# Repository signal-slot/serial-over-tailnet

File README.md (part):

# serial-over-tailnet

[日本語](README-ja.md)

An ESP32-S3 board with PSRAM that joins a Tailscale network (a tailnet) on its own and bridges the serial console of a target SBC to a TCP port on the tailnet.
The console is a 3.3 V UART of the target (with a Seeed Studio XIAO ESP32S3 or ESP32C3) or one of its USB serial interfaces (with a YD-ESP32-S3).
The project was called usb-serial-over-tailscale until November 2026.

```text
Remote PC ──Tailscale / TCP:35930────▶ XIAO ESP32S3/C3 ──UART───▶ UART console of the target SBC
Remote PC ──Tailscale / TCP:35930+n──▶ YD-ESP32-S3 ───USB host──▶ serial interface n of the target SBC
Remote PC ──Tailscale / USB/IP 3240──▶ YD-ESP32-S3 ───USB host──▶ the whole USB device (a debug probe, for example)
```

Everything a Tailscale node needs (control protocol, WireGuard, DERP, NAT traversal) is implemented in Rust in this repository.
Initial setup is an interactive shell over USB serial; flashing and setup are done from a browser, with nothing to install.

## Status

Working end to end:

- Wi-Fi setup through the wizard and joining a tailnet with the approval URL.
- `tailscale ping` from another node, both via DERP and over a direct path.
- With a XIAO ESP32S3: the console of a Raspberry Pi 5 over its 3.3 V UART (the 3-pin debug connector).
- With a XIAO ESP32C3 (no PSRAM): joining a tailnet of 50 peers, its DERP connection, 300 bridge connections in a row with memory steady, its UART in a loopback (D10 wired to D8) over the tailnet, and the console of a NanoPC-T6 on its 3.3 V debug UART at 1500000 baud, the line set by pyserial's `rfc2217://`.
- With a YD-ESP32-S3: console access to a Raspberry Pi Debug Probe (CDC-ACM) and a Toradex Dahlia (FT4232H) over USB.
- RFC 2217 sessions against both USB targets: baud rate and framing changes, DTR and RTS, break and purge from pyserial.
- On the FT4232H, three ports claimed at once and a client on the fourth port refused.
- Recovery after adapter reboot, Wi-Fi reconnection and USB replug.
- With a YD-ESP32-S3 in USB/IP mode: the MCU-Link of an FRDM-MCXN947 attached on a Linux PC with `usbip attach`, probe-rs erasing the MCXN947, writing 712 KB to its flash and verifying it, and the board's console on the MCU-Link's serial port.

Not yet:

- Headless registration with an auth key.
- CP210x, CH340/CH341, and non-H-series FTDI chips such as the FT232R.
- Recovery after a reboot of the target SBC, an internet outage, or an unreachable control server.
- Long-running operation, behaviour after node key expiry (180 days by default), and reboots triggered by the task watchdog.
- esptool through RFC 2217 (its DTR and RTS sequence is tested on the host with `cargo run -p adapter-core --example rfc2217_sim`).

### Boards and images

Flash size and PSRAM mode are build-time settings, so CI builds one image per board and module (`firmware/variants/`).
PSRAM is required on the ESP32-S3 boards: network thread stacks, TLS buffers and most of the heap live there.
The ESP32-C3 has none; its image is built with smaller stacks and buffers (feature `small-ram` of tsnode), and about 40 KB of its RAM stays free on a tailnet of 50 peers.

| Image | Board | Flash | PSRAM | Status |
| --- | --- | --- | --- | --- |
| `xiao-s3` | Seeed Studio XIAO ESP32S3 | 8 MB | 8 MB octal | supported |
| `xiao-c3` | Seeed Studio XIAO ESP32C3 | 4 MB | none | supported (UART tried in a loopback) |
| `n16r8` | YD-ESP32-S3 with an N16R8 module | 16 MB | 8 MB octal | supported |
| `n8r2` | YD-ESP32-S3 with an N8R2 module | 8 MB | 2 MB quad | supported |
| `n8r8` | YD-ESP32-S3 with an N8R8 module | 8 MB | 8 MB octal | built |
| | modules without PSRAM (N4, N8, N16) | | none | not supported |

To build an image locally, point esp-idf-sys at its defaults file and pass its name to the image script.
The XIAO's image also needs its feature; the ESP32-C3 is another target and is built without the USB host component:

```bash
cd firmware
ESP_IDF_SDKCONFIG_DEFAULTS="sdkconfig.defaults;variants/xiao-s3.defaults" cargo build --release --features board-xiao-s3
tools/mkimage.sh xiao-s3 release

MCU=esp32c3 ESP_IDF_SYS_EXTRA_COMPONENTS_FILE="$PWD/variants/no-extra-components.toml" \
ESP_IDF_SDKCONFIG_DEFAULTS="sdkconfig.defaults;variants/xiao-c3.defaults" \
  cargo build --release --features board-xiao-c3 --target riscv32imc-esp-espidf
tools/mkimage.sh xiao-c3 release

ESP_IDF_SDKCONFIG_DEFAULTS="sdkconfig.defaults;variants/n8r2.defaults" cargo build --release
tools/mkimage.sh n8r2 release
```

## Layout

| Path | Role |
| --- | --- |
| `crates/tsnode` | Tailscale node: control plane (ts2021 Noise and a minimal HTTP/2), WireGuard, DERP, disco, STUN, TCP termination with smoltcp. Runs on a host and on ESP-IDF. |
| `crates/adapter-core` | Interactive setup shell. I/O and device operations are traits, so the wizard is unit-tested on the host. |
| `tools/hostnode` | Runs tsnode on Linux for verification: joins a real tailnet and serves an echo server. |
| `firmware` | ESP32-S3 and ESP32-C3 firmware (esp-idf-svc): setup console, UART bridge (XIAO ESP32S3 and ESP32C3), USB host (YD-ESP32-S3: CDC-ACM, FTDI, CP210x, CH34x), Wi-Fi, Tailscale node, TCP bridge. |
| `hardware/case` | 3D-printed case for the YD-ESP32-S3: OpenSCAD source and ready-to-print STLs, with and without pin headers ([README](hardware/case/README.md)). |
| `hardware/xiao-carrier` | Carrier board for the XIAO ESP32S3 with level translation and a 4-pin header; designed, not made ([README](hardware/xiao-carrier/README.md)). |
| `hardware/board` | Our own adapter board around the ESP32-S3-MINI-1; ordered, not yet verified ([README](hardware/board/README.md)). |

tsnode is split into these modules.

| Module | Contents |
| --- | --- |
| `controlbase`, `h2`, `control` | `/key` fetch, Noise IK handshake over `POST /ts2021`, `/machine/register` and `/machine/map` over HTTP/2. `/key` is always TLS; the Noise transport tries plain :80 first and falls back to TLS. |
| `wireguard` | Noise IKpsk2 handshake (initiator and responder), transport, replay window, rekey and keepalive timers. |
| `derp` | DERP relay client (TLS, fast-start, ping/pong, NotePreferred). |
| `disco`, `stun` | ping, pong and call-me-maybe for direct paths; public endpoint discovery with STUN. |
| `magicsock` | Path selection between UDP and DERP, handshake handling, peer table. |
| `netstack` | TCP termination on the tailnet addresses with smoltcp. |
| `node` | Ties the above together in threads. Keys persist in NVS or a file. |

## Usage

### Prepare the board

Two boards can be used; which one depends on where the target's console is.

| Board | Bridges | Soldering |
| --- | --- | --- |
| Seeed Studio XIAO ESP32S3 | a 3.3 V UART of the target (pins or a debug connector) | none on a board that comes with pin headers |
| Seeed Studio XIAO ESP32C3 | the same, on other pins | the same |
| YD-ESP32-S3 | a USB serial interface of the target (its debug USB port) | required (the `USB-OTG` pad on the back) |

#### Seeed Studio XIAO ESP32S3

Buy a [Seeed Studio XIAO ESP32S3](https://www.seeedstudio.com/XIAO-ESP32S3-p-5627.html).
It has one USB-C port and no USB host role here: it bridges a **3.3 V UART** instead of a USB serial adapter, on port 35930.
Use it when the target has a UART on pins or a debug connector, such as the 3-pin debug connector of a Raspberry Pi 5.

| XIAO pin | Role | Connect to |
| --- | --- | --- |
| `GND` | ground | the target's GND |
| `3V3` | not used | leave unconnected |
| `D10` | TX (out of the XIAO) | the target's RX |
| `D9` | RX (into the XIAO) | the target's TX |

The four pins are next to each other on one side of the board (from the USB-C end: 5V, GND, 3V3, D10, D9, D8, D7).
On a board that comes with pin headers, jumper wires plug straight onto them; on a bare board, solder a 4-pin socket or pin header there.
The UART is 3.3 V only: do not connect 5 V or RS-232 signals, and put a level translator in between for a 1.8 V target.
Attach the antenna that comes with the board.

On the installer page it is the first entry under "Choose your board".
If no serial port appears, hold the `B` (BOOT) button while plugging the board in.
The USB port stays the setup console after setup as well (there is no second port), and it powers the board: a charger or a USB port of the target will do.
The baud rate is set with `baud` (115200 by default) or by an RFC 2217 client; there are no DTR and RTS lines.

Verified with the plain XIAO ESP32S3 on a Raspberry Pi 5; the Sense and Plus versions have not been tried.
The firmware limits the Wi-Fi transmit power to 15 dBm on this board: at 19.5 dBm and above it did not get past association with two access points, and at 18 dBm and below it did.
In Japan the board is sold with 技適: construction design certification number 217-230892, as [Akizuki Denshi lists it](https://akizukidenshi.com/catalog/g/g118078/). Elsewhere, check the marking on the board and the rules that apply to you.
[`hardware/xiao-carrier/`](hardware/xiao-carrier/) is a small carrier board for it (not made yet).

#### Seeed Studio XIAO ESP32C3

The [XIAO ESP32C3](https://wiki.seeedstudio.com/XIAO_ESP32C3_Getting_Started/) has the same outline and is used the same way, with these differences:

| XIAO pin | Role | Connect to |
| --- | --- | --- |
| `GND` | ground | the target's GND |
| `D10` | TX (out of the XIAO) | the target's RX |
| `D9` | not used | leave unconnected |
| `D8` | RX (into the XIAO) | the target's TX |

The pins are on the same side as on the S3 (from the USB-C end: 5V, GND, 3V3, D10, D9, D8, D7); a 5-pin socket from GND to D8 covers them.
RX is on D8 instead of D9 because the C3's D9 is GPIO9: the BOOT button pulls it to ground, and the chip starts in download mode if it is low at reset.
The carrier board connects D9, so it does not fit the C3.

Its ESP32-C3 has no PSRAM, so the firmware keeps less: only a few endpoints per peer, a peer's WireGuard state only once the peer talks to it, and a TCP window of 2 KB on the tailnet.
It has joined a tailnet of 50 peers with about 40 KB of RAM to spare; a much larger tailnet may not fit.
Its UART has been tried in a loopback, not yet against a target.
In Japan the board is sold with 技適: construction design certification number 204-B00704, as [Akizuki Denshi lists it](https://akizukidenshi.com/catalog/g/g117454/).

#### YD-ESP32-S3

Buy the [**YD-ESP32-S3** from VCC-GND Studio (its page on AliExpress)](https://www.aliexpress.com/item/1005004025123046.html).
On that page choose **N16R8** or **N8R2**: those two are supported.
The board has two USB-C ports, labelled `COM` and `USB` ([photos and documents from its maker](https://github.com/vcc-gnd/YD-ESP32-S3)).

**A note on radio certification.** The YD-ESP32-S3 is a good, inexpensive board. One thing to know before buying: its Wi-Fi module (marked `ESP32-S3-N16R8` or `ESP32-S3-N8R2`) is not one of Espressif's certified modules. It has no Japanese 技適 (we looked it up in the MIC database), and we have not found a radio certification for it in any other country either. Whether that matters depends on where you are: many countries put the obligation on sellers rather than on hobbyists, so please check the rules that apply to you. In Japan, the Radio Act asks the user's own equipment to carry the 技適 mark, so this board cannot be used there; for Japan we are making a board around the certified ESP32-S3-MINI-1 module, see [`hardware/board/`](hardware/board/) (designed and ordered in November 2026, not yet verified).

Short the `USB-OTG` solder pad on the back of the board (shown below before bridging).

This is required: it feeds 5 V from the board to the target's USB port, and without it the target chip never powers up and is never detected.
The two ports have fixed roles: **`COM` = 5 V power in** (a charger or a PC), **`USB` = the SBC** (the target's debug USB port). For flashing and setup, `COM` goes to the PC (it powers the board as well); `USB` can stay on the SBC.
See "Power and wiring" below for the safety rule that follows from it.

### Flash from a browser

Open [signal-slot.github.io/serial-over-tailnet](https://signal-slot.github.io/serial-over-tailnet/) in Chrome or Edge to flash and configure the board without installing anything.
The page opens the board's serial port with WebSerial and writes the CI-built binaries with ESP Web Tools (esptool-js).
A terminal on the same page runs the setup wizard.
It works on Windows 10 and later, macOS, Linux and ChromeOS; it does not work in Firefox, Safari or on phones.

Choose the board at the top of the page.

- **XIAO ESP32S3**: connect its USB-C port to the PC. It shows up as `USB JTAG/serial debug unit` (303a:1001). If no port appears, unplug it, hold the `B` (BOOT) button and plug it in again.
- **YD-ESP32-S3**: choose the module from the marking on its metal can (for example `ESP32-S3-N16R8`) and connect the `COM` port (CH343, 1a86:55d3). It flashes through the board's auto-download circuit, carries the boot log, and the target can stay plugged into the native port. The native port (303a:1001) works too and starts the wizard as soon as a terminal opens, but it disappears when setup completes and the port becomes the USB host; use it if the operating system does not list the COM port.

CI (GitHub Actions) builds every image on each push. Tags matching `v*` also attach `serial-over-tailnet-<image>.bin` (bootloader, partition table and app merged into one file) to a release.
The merged file can be written with `esptool write_flash 0x0`, but it also overwrites the NVS area with 0xFF, which erases the configuration and registration.
Updates from the page write only the three regions and keep the configuration.

### Initial setup

An unconfigured board plugged into a PC shows up as a USB serial port (Espressif USB JTAG/serial, 303a:1001): the XIAO's only port, the YD-ESP32-S3's native port.
Open it in a terminal and press Enter to start the wizard.
On the XIAO this port stays the shell after setup too, quiet until a command is typed.
On the YD-ESP32-S3 the COM port carries the same shell at 115200 together with the log output; it stays quiet until Enter, and `setup` starts the wizard there.

```bash
screen /dev/ttyACM0 115200
```

Leave DTR and RTS as a terminal leaves them, both asserted.
On these ports they reset the chip and select its boot mode, so a tool that
drives them apart resets the board, possibly into the ROM download mode, where
it goes quiet and answers nothing.

```text
serial-over-tailnet 0.1.0 - setup mode
Press Enter to start setup, or type a command:
=== Setup ===
Scanning Wi-Fi...
   1) home-wifi        (-48 dBm)
Select network number, or type an SSID (Enter to rescan, q to quit): 1
Password for home-wifi: ********
Connected (192.168.1.42)
Hostname on the tailnet [target-console]:
Registering with Tailscale... (press q to stop waiting)
Open this URL in a browser to approve the device:
  https://login.tailscale.com/a/xxxxxxxx
Waiting for approval...
Tailscale is up: target-console.example.ts.net 100.x.y.z
Setup complete. Reboot into normal mode now? [Y/n]
```

`setup` only adds a Wi-Fi network when the hostname and the Tailscale registration are already done.
`setup all` starts over.
To use an auth key, run `authkey tskey-auth-...` and then `login`.

The main commands are listed below; `help` prints the full list.

| Command | Description |
| --- | --- |
| `wifi <ssid> <pw>` | Add a Wi-Fi network and connect. Several can be stored; the strongest known AP is chosen at boot and on reconnect. |
| `wifi list`, `wifi forget <ssid>` | List and remove stored networks. |
| `port <n>`, `baud <rate>` | TCP port (default 35930; on the YD-ESP32-S3, USB interface n of the target is served on port+n) and baud rate of the target (default 115200). |
| `usbdrv <auto\|cdc\|ftdi\|cp210x\|ch34x>` | YD-ESP32-S3 only: USB-serial bridge chip. The default detects it from VID and PID. |
| `usbdrv usbip` | YD-ESP32-S3 only: export the whole USB device over USB/IP instead (see "USB/IP"). `usbdrv auto` goes back to the serial bridge. Takes effect after `reboot`. |
| `status`, `reset`, `reboot` | Show status, erase configuration and keys, reboot. |

On the XIAO the shell is always on the USB port, so any command, `setup` included, can be run at any time; the log goes to UART0 on pins D6 (TX) and D7 (RX) at 115200 bps.
On the YD-ESP32-S3 the same shell is always available on the COM port (115200 bps, shared with the log): press Enter to get a prompt.
Holding BOOT while the firmware starts enters setup mode again.

### Connecting

The XIAO ESP32S3 serves its UART on one TCP port: 35930, unless `port` changed it.

With a YD-ESP32-S3, every serial interface of the target is served on its own TCP port: the first port plus the USB interface number.
Which interfaces those are is read from the device when it is plugged in, so nothing has to be configured.

| Target | Interface | Port |
| --- | --- | --- |
| A plain CDC-ACM console (one function) | 0 | 35930 |
| Raspberry Pi Debug Probe (interface 0 is CMSIS-DAP) | 1 | 35931 |
| Toradex Dahlia, MCU console (FT4232H port C) | 2 | 35932 |
| Toradex Dahlia, Verdin console (FT4232H port D) | 3 | 35933 |

From any machine on the tailnet, open a raw TCP connection to that port of the hostname or tailnet address, or an RFC 2217 (Telnet) one.

```bash
socat -,rawer,escape=0x1d TCP:target-console:35930   # Ctrl-] to exit
nc target-console 35930
python -m serial.tools.miniterm rfc2217://target-console:35930 9600   # RFC 2217: the client sets the line
esptool --port rfc2217://target-console:35930 flash_id                 # YD-ESP32-S3: DTR and RTS reset an ESP32 target
```

One connection at a time is served per port.
A second connection while one is active receives `busy` and is closed.
A peer that stops responding is dropped after 120 seconds and the next connection is accepted.

The first byte the client sends decides what the session is.
A client that opens with Telnet negotiation (IAC, 0xFF), as pyserial's `rfc2217://` and esptool do, gets an RFC 2217 session: it can set the baud rate, data bits, parity and stop bits, drive DTR and RTS, hold a break and purge the receive buffer, and every setting is answered with the value in force, so a refused one is visible to the client.
The settings last until the client disconnects; the next session starts again from the adapter's `baud` and 8N1 with DTR and RTS asserted.
Flow control is reported as none, and modem-state and line-state notifications are not sent.
Anything else is a raw session: bytes flow unchanged in both directions, there is no protocol on top, and the baud rate is the adapter's setting.
A `telnet` client that negotiates first (netkit, inetutils) gets an RFC 2217 session in character mode; the BSD one waits for the server to speak first and so gets a raw session in line mode.
Bytes the target sends before the client's first byte go out unframed in either case.
On the XIAO's UART there are no DTR and RTS lines (requests are accepted and do nothing), a break is made by holding TX low, and mark and space parity are refused.

With a YD-ESP32-S3 the ports are independent: each has its own USB interface, its own busy state and its own line settings, and a client on one port does not block another.
They share one USB device and one tailnet address.
The USB interface is claimed when the first client connects to its port and stays claimed after the client leaves; output from the target is dropped while nobody is connected.
The ESP32-S3's host controller has eight pipes, one for control and two per claimed interface (three for CDC-ACM), so at most three ports of an FT4232H can be claimed, and the claims last until the device is unplugged or the adapter reboots. A client on a fourth port is told `usb: cannot open the interface: no free USB host pipe` and closed.
`status` on the shell lists the interfaces with their ports, marks the open ones with their line settings and the idle claimed ones with `claimed`.

### USB/IP

With `usbdrv usbip`, a YD-ESP32-S3 exports the whole device on its USB port over USB/IP (TCP 3240), instead of bridging its serial interfaces.
A Linux PC on the tailnet attaches it with the standard `usbip` tool, and from then on the PC's own drivers and tools see the device as if it were plugged in: a debug probe's CMSIS-DAP or vendor protocol, and its serial ports.

```bash
sudo modprobe vhci-hcd
usbip list -r target-console                 # the device, as bus ID 1-1
sudo usbip attach -r target-console -b 1-1
probe-rs list                                # the probe is there
sudo usbip detach -p 0                       # port number from `usbip port`
```

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
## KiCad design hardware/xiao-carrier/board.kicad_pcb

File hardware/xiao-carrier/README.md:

# XIAO carrier

A small board that a Seeed Studio XIAO ESP32S3 sits on.
A XIAO ESP32C3 has the same outline but does not fit: this board takes RX on D9, and on the C3 the firmware takes it on D8, because the C3's D9 is the BOOT button's pin.
Past the XIAO's end opposite the USB-C connector it has a 4-pin right-angle header with a UART at the target's voltage.

**Not made yet.** Nothing here has been tested on hardware.

| | |
|---|---|
| Size | 20.0 × 31.7 mm, 2 layers |
| Header | G, TX, RX, V (2.54 mm, right angle), the order of the adapter board in `../board` |
| V | the target's supply, 1.65 to 5.5 V; it powers the target side of the level translators and nothing else |
| XIAO pins | D10 = TX, D9 = RX, as in the firmware (`board-xiao-s3`); D1 = V / 2 for the ADC, which the firmware does not read yet |
| Level translators | 2 × SN74LVC1T45, 330 Ω in series with TX and RX |
| Solder jumper | on the bottom, open as made; bridged, it connects V to the XIAO's 3.3 V for a 3.3 V target wired with G, TX, RX only |

The XIAO's lands have holes.
It is soldered flat on the board by its castellated edge, or stands on pin headers.
Under the XIAO the top layer has no copper but the lands, because the XIAO's underside has bare pads.

Never bridge the jumper and wire V to the target at the same time: that joins two supplies.

## Files

`design.py` is the single source (parts, JLCPCB part numbers, nets) and `layout.py` places the parts.
The scripts shared with the adapter board are in `../board`.

```bash
python3 ../board/gen_sch.py .            # board.kicad_sch
python3 gen_pcb.py                       # board.kicad_pcb: footprints, rules
python3 route.py export work/board.dsn
java -Djava.awt.headless=true -jar freerouting.jar --gui.enabled=false \
    -de work/board.dsn -do routing.ses -mp 20 -mt 1
python3 route.py import routing.ses      # tracks, vias, ground fill
kicad-cli pcb drc --severity-all -o drc.rpt board.kicad_pcb
python3 ../board/fab.py .                # fab/: gerbers.zip, bom.csv, cpl.csv
```

`routing.ses` is kept because routing again gives a different result.
JLCPCB assembles the top side; the XIAO is soldered on by hand.

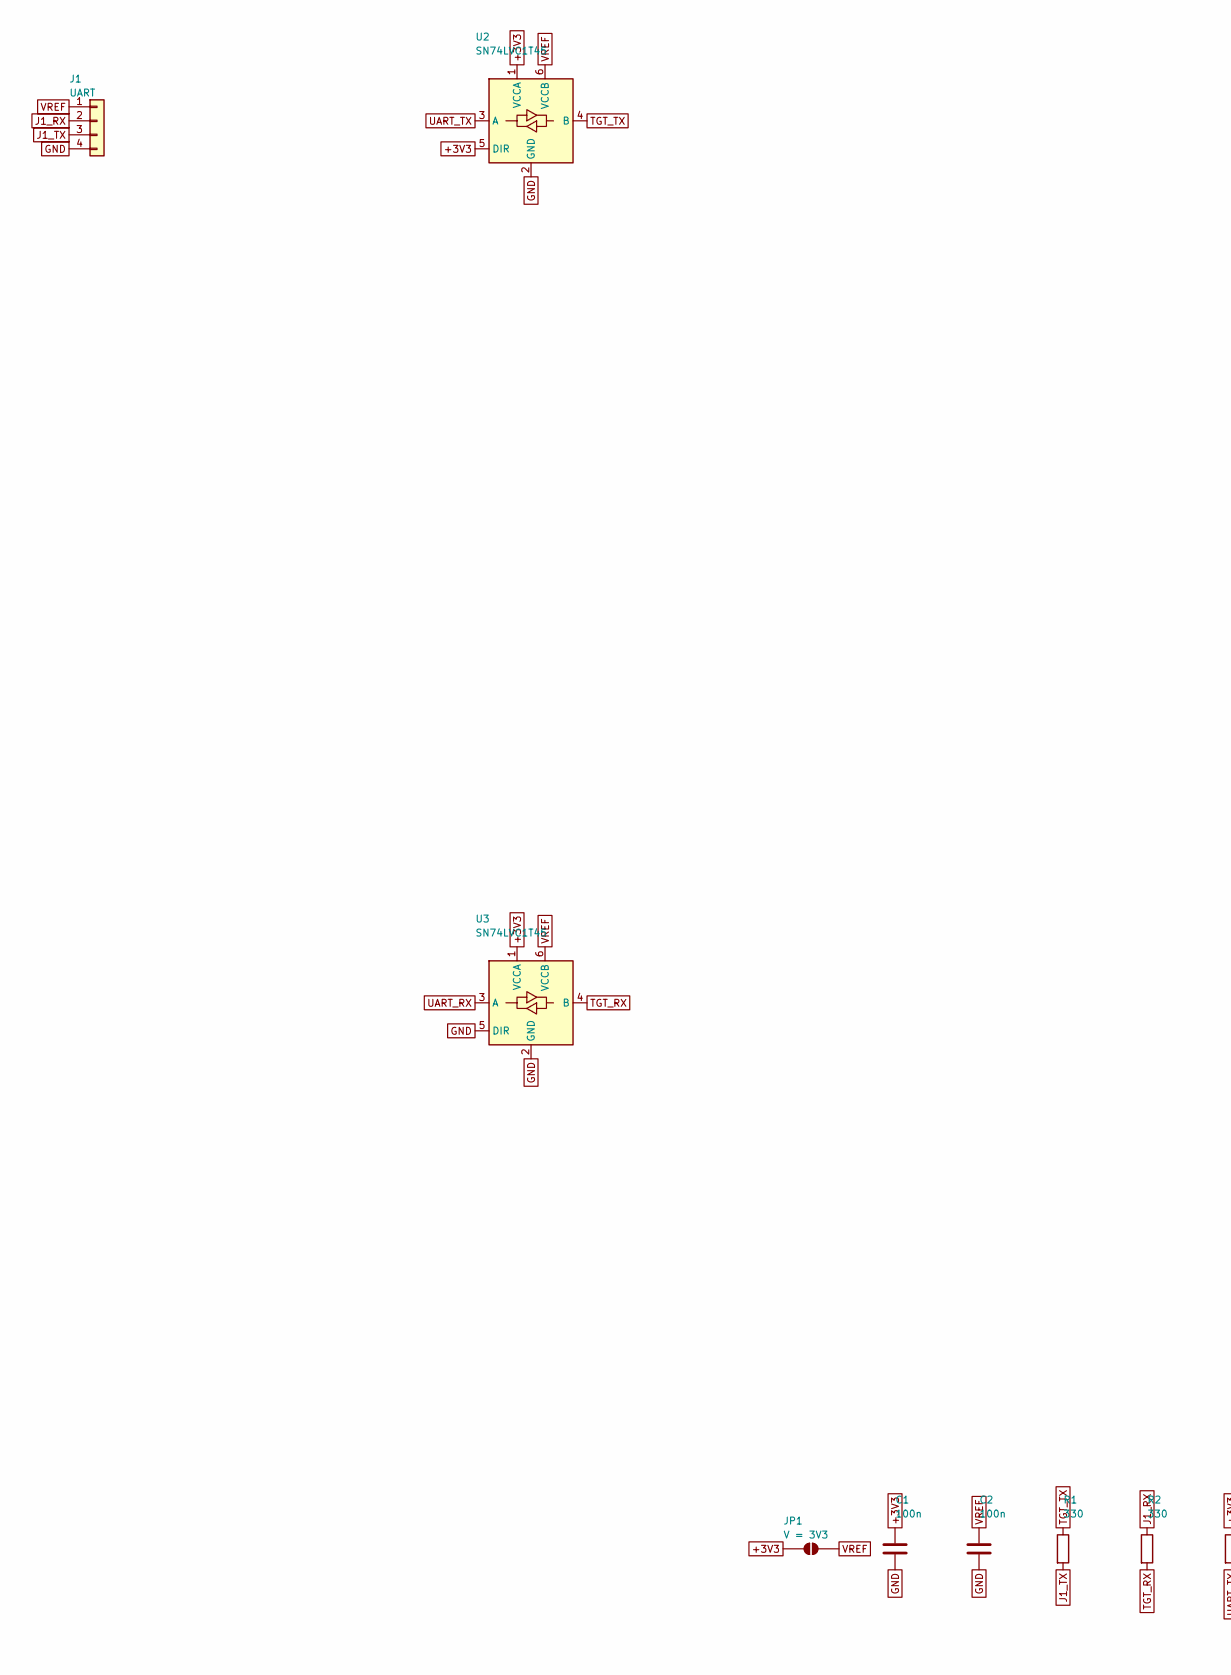
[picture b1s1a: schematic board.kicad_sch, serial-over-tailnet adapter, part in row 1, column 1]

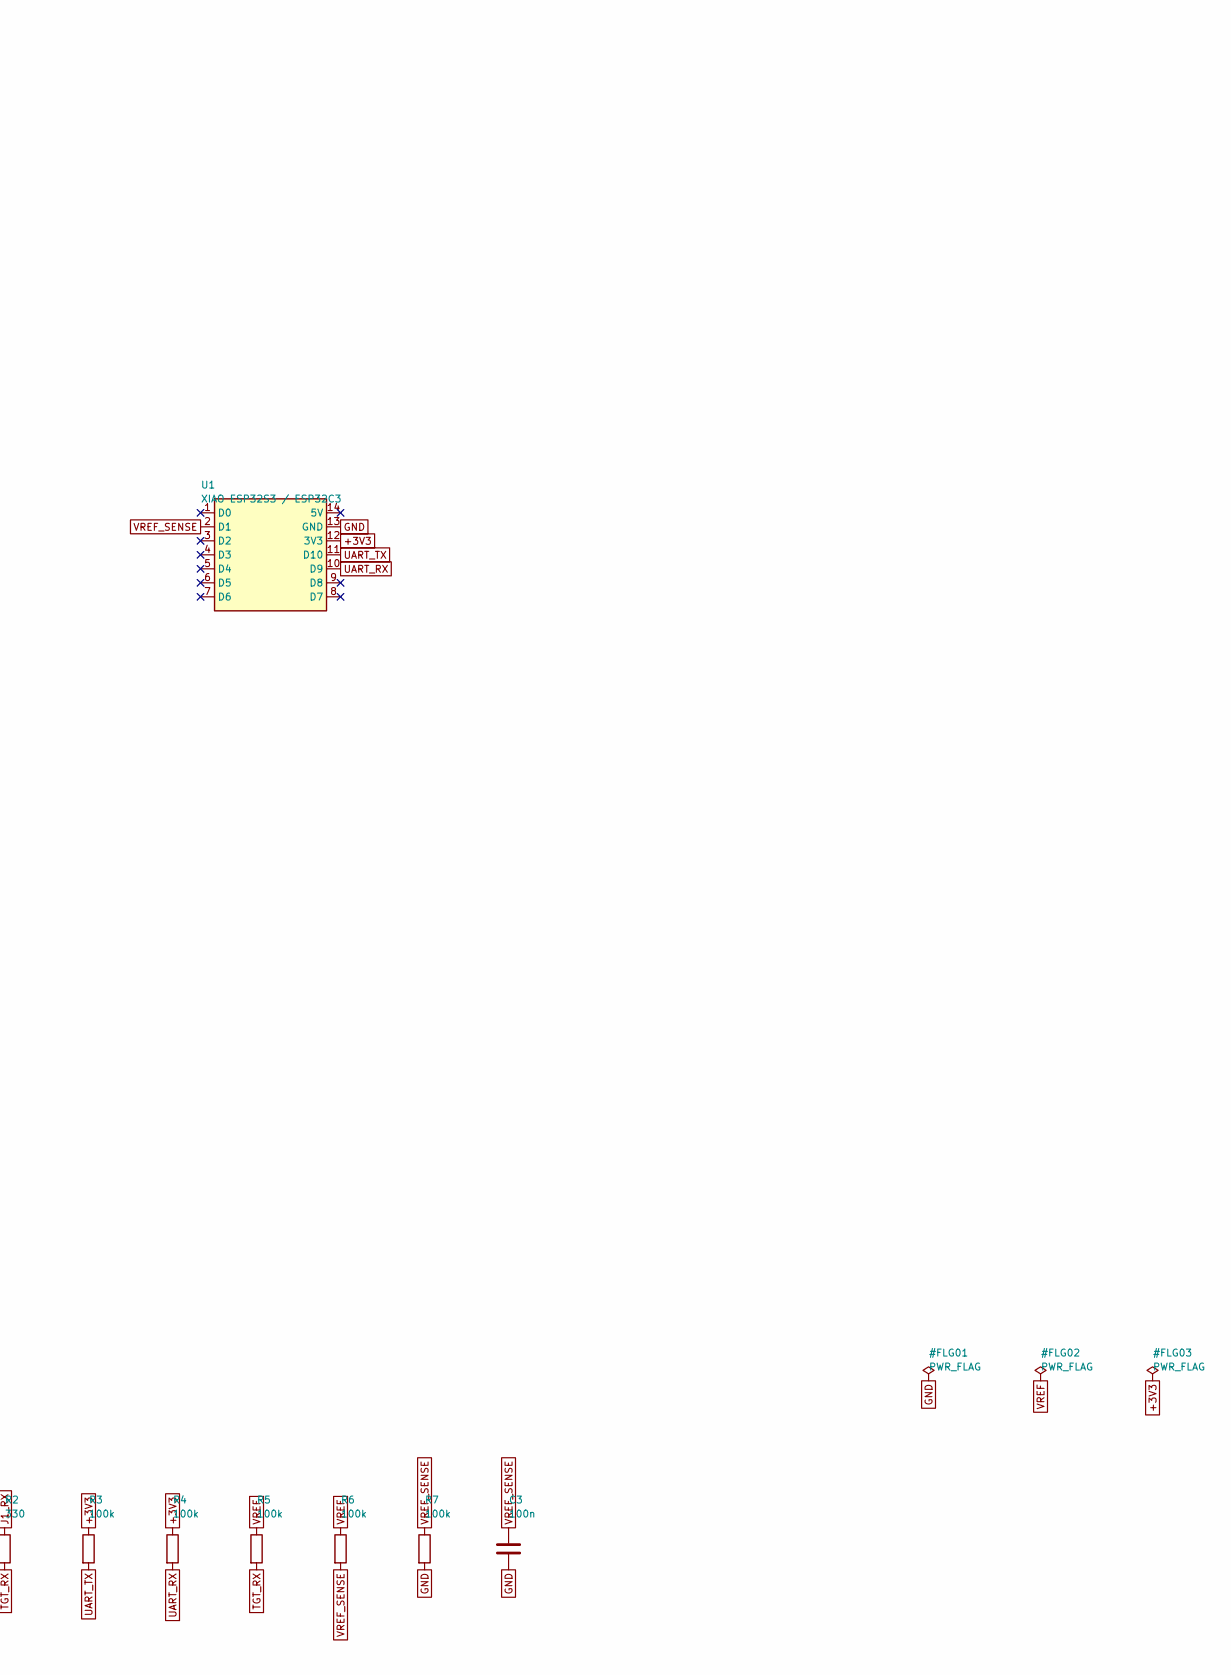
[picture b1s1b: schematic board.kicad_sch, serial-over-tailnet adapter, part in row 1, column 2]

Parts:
C1, C2, C3: 100n; C_0402_1005Metric; LCSC C1525
J1: UART; PinHeader_1x04_P2.54mm_Horizontal; LCSC C32713263
JP1: V = 3V3; SolderJumper-2_P1.3mm_Open_RoundedPad1.0x1.5mm
R1, R2: 330; R_0402_1005Metric; LCSC C25104
R3, R4, R5, R6, R7: 100k; R_0402_1005Metric; LCSC C25741
U1: XIAO ESP32S3 / ESP32C3; XIAO
U2, U3: SN74LVC1T45; SOT-363_SC-70-6; LCSC C9382

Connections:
+3V3: C1.1, JP1.1 (A), R3.1, R4.1, U1.12 (3V3), U2.1 (VCCA), U2.5 (DIR), U3.1 (VCCA)
GND: C1.2, C2.2, C3.2, J1.4, R7.2, U1.13 (GND), U2.2 (GND), U3.2 (GND), U3.5 (DIR)
J1_RX: J1.2, R2.1
J1_TX: J1.3, R1.2
TGT_RX: R2.2, R5.2, U3.4 (B)
TGT_TX: R1.1, U2.4 (B)
UART_RX: R4.2, U1.10 (D9), U3.3 (A)
UART_TX: R3.2, U1.11 (D10), U2.3 (A)
VREF: C2.1, J1.1, JP1.2 (B), R5.1, R6.1, U2.6 (VCCB), U3.6 (VCCB)
VREF_SENSE: C3.1, R6.2, R7.1, U1.2 (D1)

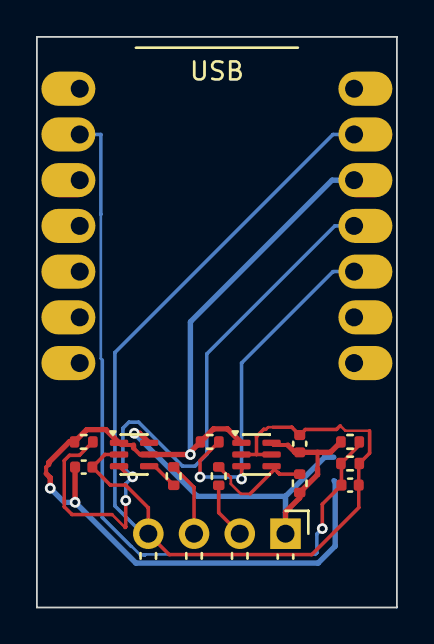
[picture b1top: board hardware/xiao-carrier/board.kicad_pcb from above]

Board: 2 copper layers, 20.0 x 31.7 mm, 15 parts (1 on the bottom side), 10 nets.

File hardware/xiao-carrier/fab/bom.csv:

Comment,Designator,Footprint,LCSC Part #
SN74LVC1T45,"U2,U3",SOT-363_SC-70-6,C9382
UART,J1,PinHeader_1x04_P2.54mm_Horizontal,C32713263
100n,"C1,C2,C3",C_0402_1005Metric,C1525
330,"R1,R2",R_0402_1005Metric,C25104
100k,"R3,R4,R5,R6,R7",R_0402_1005Metric,C25741

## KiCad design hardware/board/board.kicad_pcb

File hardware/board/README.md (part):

# Adapter board

A board of our own for the adapter, around the ESP32-S3-MINI-1-N4R2 module, which carries
the Japanese radio certification (技適 201-230385) that the YD-ESP32-S3 boards we tested
on do not.

*The design has not been built or tested yet. Everything below about how it behaves is
what the schematic says, not what a board did.*

[日本語](README-ja.md)

## What it is

- 35.1 × 26.7 mm, four layers, parts on both sides, 68 parts, all placed by JLCPCB
  (Standard assembly: the module and the TUSB320 are "Standard only" parts there, and
  the board has parts on both sides).
- Two identical USB-C ports, one at each end. Either one can be the port the PC side
  plugs into; the other then powers and talks to the target. A TUSB320LAI per port reads
  the cable's orientation and role over I2C, an LM66200 picks whichever port delivers
  5 V, and a TS3USB221 switches the module's USB to the other port. The LM66200's status
  output sets the switch's default, so the board routes the right way even before the
  firmware runs. 5 V to the target goes through an AP22653 current limiter (490 mA) per
  port, which the firmware turns on while that port's detector sees a sink attached.
- A 2.54 mm right-angle pin header (on the top, pins out of the long edge) for a
  target's UART: G, TX, RX, V. TX and RX go through two SN74LVC1T45 level translators
  whose target side is supplied by VREF, so a 1.8 V or 3.3 V target works; 330 Ω in
  series keeps a TX-to-TX miswire harmless. VREF comes from the header's V pin, or from the board's
  3.3 V when the slide switch next to the header is on `3V3` (for a target wired with
  three wires only). The module measures VREF on IO1.
- USB ESD protection (USBLC6-2SC6) on both ports, a BOOT button, a red LED, test pads for
  the module's UART0, EN, 5 V, 3.3 V and ground.
- The module's antenna sits over a 5 mm strip of bare board, without copper on any layer;
  the copper starts 0.3 mm below the antenna area. Espressif prefers the antenna beyond
  the board edge; the range with this arrangement is to be measured.

Parts, with JLCPCB numbers, are in `design.py`. The pin assignment of the module is there
too, chosen by which side of the module each signal's part sits on.

## Files

| File | What |
|---|---|
| `design.py` | The design, once: every part with its footprint, JLCPCB number and the net of every pin. |
| `layout.py` | Where every part sits, in millimetres. |
| `gen_sch.py` | Writes `board.kicad_sch`, `local.kicad_sym` and `sym-lib-table` from `design.py`. |
| `gen_pcb.py` | Writes `board.kicad_pcb` from `design.py` and `layout.py`: outline, footprints, rules, the ground plane. No tracks. |
| `route.py` | `export` writes the Specctra file for Freerouting; `import` rebuilds the board from `gen_pcb.py` and adds the router's tracks, widens the 3.3 V tracks where there is room, pours ground on every layer and stitches the pours with vias. |
| `routing.ses` | Freerouting's result. Kept because routing again gives a different result. |
| `fab.py` | Writes `fab/`: `gerbers.zip`, `bom.csv`, `cpl.csv` and `placement-check.txt` for JLCPCB. Refuses a board that fails KiCad's check, or a part whose JLCPCB footprint would not land on its pads. |
| `jlc_align.py`, `jlc_transforms.json` | JLCPCB's footprint for every part number, matched to KiCad's: the rotation and origin `fab.py` writes. The script needs the network; the result is kept. |
| `local.pretty/`, `local.kicad_sym` | The footprint of the slide switch (from the maker's drawing) and the symbols KiCad's libraries lack. |
| `board.kicad_pcb`, `board.kicad_sch`, `board.kicad_pro` | The result, as KiCad 10 opens it. |
| `sexpr.py` | A small S-expression reader and writer the scripts share. |

## Rebuilding

Needs KiCad 10 with its Python module (`import pcbnew`), KiCad's symbol and footprint
libraries, and Java for Freerouting (tested with 2.5.0).

```bash
python3 gen_sch.py && kicad-cli sch erc -o erc.rpt board.kicad_sch     # 0 errors, 0 warnings
python3 route.py import routing.ses                                    # board.kicad_pcb
kicad-cli pcb drc --severity-all -o drc.rpt board.kicad_pcb            # 0 violations, 0 unconnected
python3 fab.py                                                         # fab/
```

To route again after a change to the parts or the layout:

```bash
python3 gen_pcb.py
python3 route.py export work/board.dsn
java -jar freerouting.jar -de work/board.dsn -do routing.ses -mp 60 -mt 1
python3 route.py import routing.ses
```

Freerouting does not finish every time (on this board it finished on about half of the
attempts, and some of those left a piece of ground fill unconnected). `BOARD_LENGTH=35.4
python3 gen_pcb.py` moves the parts for another board length, which is the cheap way to
get another attempt. Check with `kicad-cli pcb drc` and keep the session file that passes.

## Firmware

The firmware is built for this board with its own variant and feature (the default
build is for the YD-ESP32-S3 development board):

```bash
cd firmware
ESP_IDF_SDKCONFIG_DEFAULTS="sdkconfig.defaults;variants/adapter.defaults" cargo build --release --features board-adapter
tools/mkimage.sh adapter release        # dist/adapter/
```

What it does on this board (`firmware/src/board.rs`, `uart_link.rs`): it reads which port
supplies the 5 V (the PC's), sends the module's USB to the other port, fixes the roles of
the two detectors over I2C (the PC's port a sink, the target's a source) and turns the
target port's 5 V on while a sink is attached there and off when it leaves. In setup mode
the USB stays at the PC's port, where the console is, and no 5 V goes out. The UART header
is bridged on the first TCP port plus 8, above the interface numbers a USB device can
have, at the configured baud rate. `status` shows which port powers the board, the role
each port's detector reports, the 5 V switches' fault outputs, whether the PC's port
advertises only 500 mA (the module and a target together can exceed that), and the VREF
voltage.

## Ordering from JLCPCB

Upload `fab/gerbers.zip`, choose 4 layers, 1.6 mm, ENIG (there is a 0.4 mm pitch part),
Standard assembly for both sides, then upload `fab/bom.csv` and `fab/cpl.csv`.

JLCPCB places a part by its own footprint, whose origin and zero rotation differ from
KiCad's part by part (two SOT-23-6 parts in its library face different ways). `cpl.csv`
is therefore computed from JLCPCB's footprints: `jlc_align.py` reads them for every part
number (EasyEDA's public API; the result is `jlc_transforms.json`) and matches their pads
to KiCad's, and `fab.py` writes JLCPCB's origin and rotation for each part and then checks
that JLCPCB's pads, placed as written, cover KiCad's pads (`fab/placement-check.txt`: the
largest miss per part, 0.36 mm at most, which is the difference between JLCPCB's drawing
of the slide switch and the maker's). For bottom parts the angle is the part's
rotation as seen from the bottom (JLCPCB rotates its footprint, then mirrors it); two
placement previews on 2026-11-09 settled that, the second one through the three parts
whose JLCPCB footprint is turned 90° from KiCad's. The
LED's pads are matched so that JLCPCB's cathode (pin 2 in its symbol) lands on KiCad's.
Look at the placement preview before paying anyway; it is the only view of what JLCPCB
will do.

Rough cost, from JLCPCB's price lists in November 2026 and not from a quote: about 160 USD
for five boards (Standard assembly on both sides, about 10 USD of parts per board, a
loading fee for each of the dozen "extended" part types, hand soldering for the header).

## Design rules

Within JLCPCB's published capabilities for a 4-layer board: 0.15 mm tracks (0.09 mm
where the router had to neck down to a pad; JLCPCB's minimum is 0.09), 0.127 mm
clearance, 0.3 mm drill / 0.5 mm vias, 0.25 mm from copper to the board edge (JLCPCB asks
0.2). Supply tracks are 0.25 mm.

## Not verified

- No board has been made. The circuit, the firmware's control of it and the radio range
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
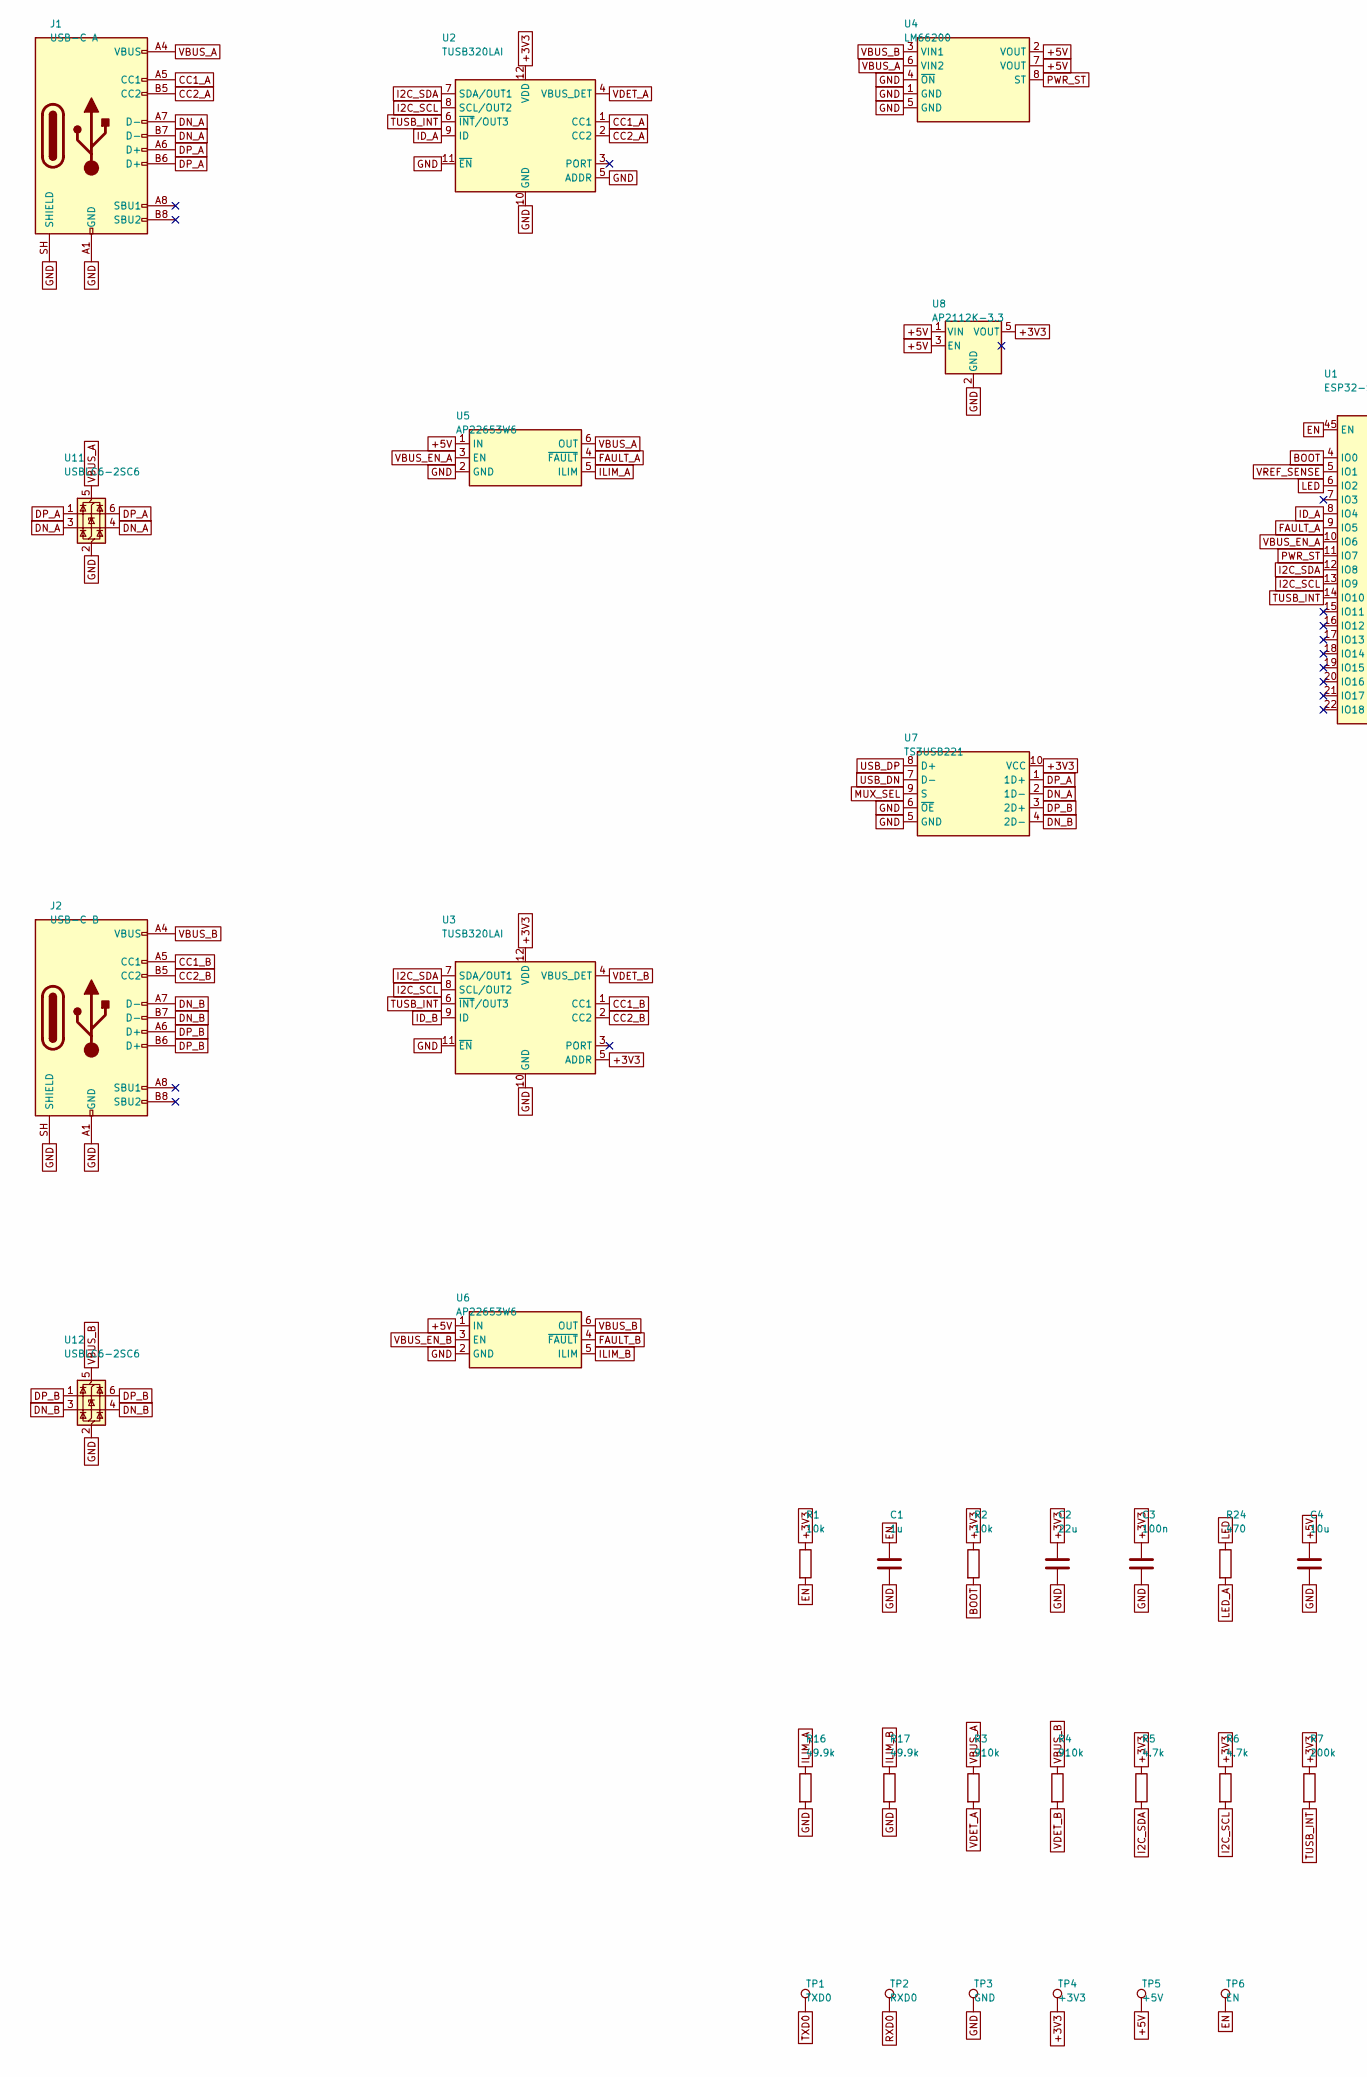
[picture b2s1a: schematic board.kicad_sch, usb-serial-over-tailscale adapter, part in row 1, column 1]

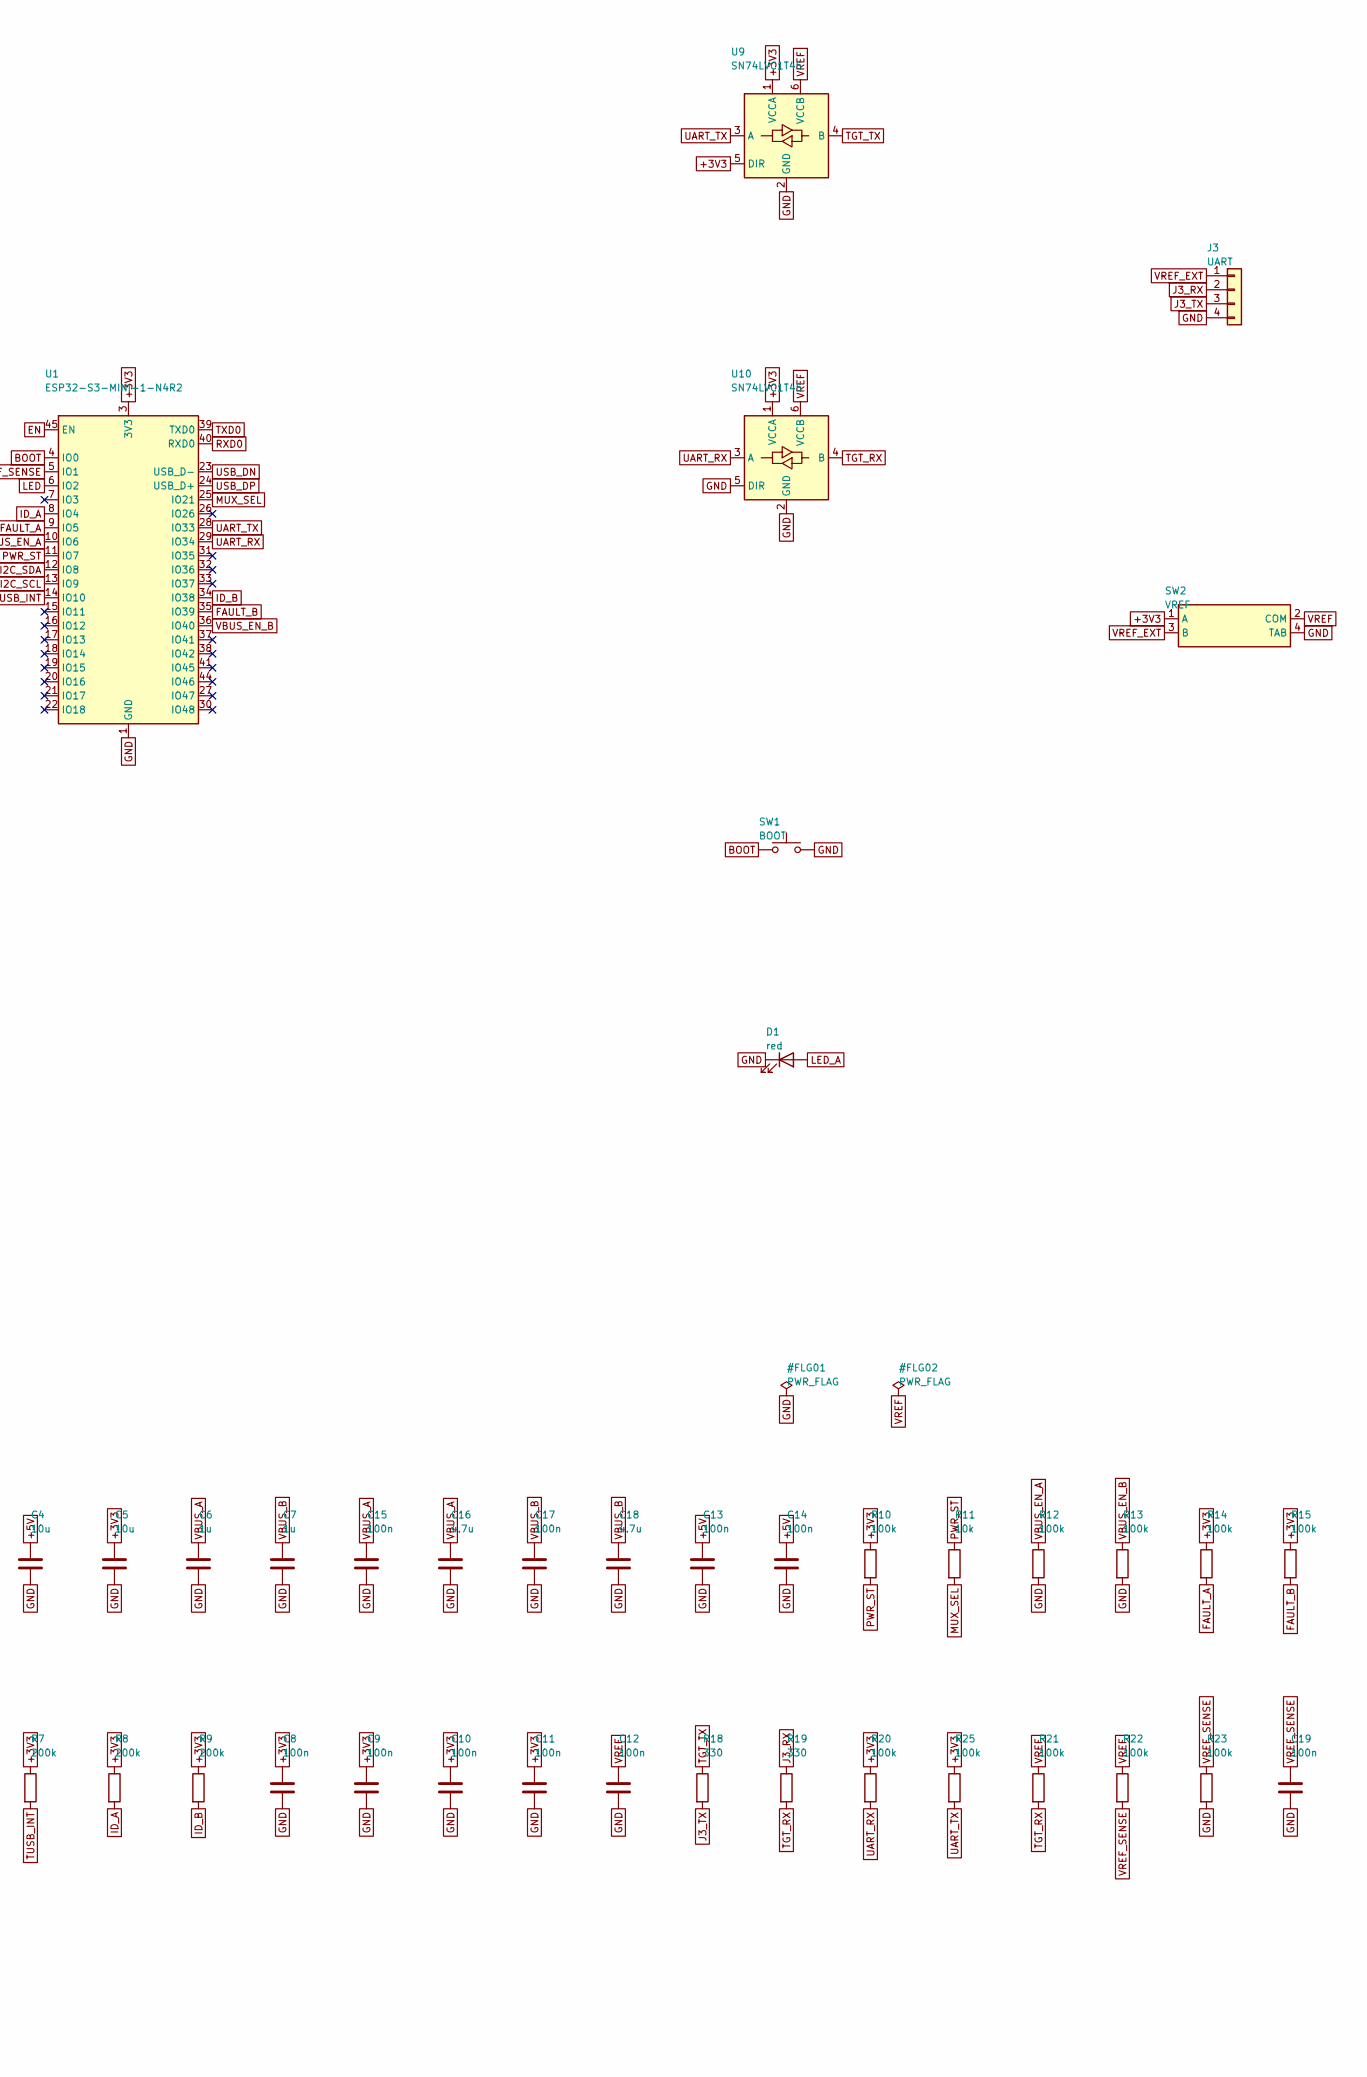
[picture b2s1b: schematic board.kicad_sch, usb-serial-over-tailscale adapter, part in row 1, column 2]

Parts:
C1, C6, C7: 1u; C_0402_1005Metric; LCSC C52923
C2: 22u; C_0603_1608Metric; LCSC C59461
C3, C8, C9, C10, C11, C12, C13, C14, C15, C17, C19: 100n; C_0402_1005Metric; LCSC C1525
C4, C5: 10u; C_0603_1608Metric; LCSC C19702
C16, C18: 4.7u; C_0603_1608Metric; LCSC C19666
D1: red; LED_0603_1608Metric; LCSC C2286
J1: USB-C A; USB_C_Receptacle_HRO_TYPE-C-31-M-12; LCSC C165948
J2: USB-C B; USB_C_Receptacle_HRO_TYPE-C-31-M-12; LCSC C165948
J3: UART; PinHeader_1x04_P2.54mm_Horizontal; LCSC C32713263
R1, R2, R11: 10k; R_0402_1005Metric; LCSC C25744
R3, R4: 910k; R_0402_1005Metric; LCSC C25800
R5, R6: 4.7k; R_0402_1005Metric; LCSC C25900
R7, R8, R9: 200k; R_0402_1005Metric; LCSC C25764
R10, R12, R13, R14, R15, R20, R21, R22, R23, R25: 100k; R_0402_1005Metric; LCSC C25741
R16, R17: 49.9k; R_0402_1005Metric; LCSC C25897
R18, R19: 330; R_0402_1005Metric; LCSC C25104
R24: 470; R_0402_1005Metric; LCSC C25117
SW1: BOOT; SW_Push_1P1T_XKB_TS-1187A; LCSC C318884
SW2: VREF; MSK12C02; LCSC C431540
TP1: TXD0; TestPoint_Pad_D1.0mm
TP2: RXD0; TestPoint_Pad_D1.0mm
TP3: GND; TestPoint_Pad_D1.0mm
TP4: +3V3; TestPoint_Pad_D1.0mm
TP5: +5V; TestPoint_Pad_D1.0mm
TP6: EN; TestPoint_Pad_D1.0mm
U1: ESP32-S3-MINI-1-N4R2; ESP32-S2-MINI-1; LCSC C3013941
U2, U3: TUSB320LAI; Texas_X2QFN-12_1.6x1.6mm_P0.4mm; LCSC C132554
U4: LM66200; SOT-583-8; LCSC C3235556
U5, U6: AP22653W6; SOT-23-6; LCSC C2158037
U7: TS3USB221; Texas_UQFN-10_1.5x2mm_P0.5mm; LCSC C130085
U8: AP2112K-3.3; SOT-23-5; LCSC C51118
U9, U10: SN74LVC1T45; SOT-363_SC-70-6; LCSC C9382
U11, U12: USBLC6-2SC6; SOT-23-6; LCSC C7519

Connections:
+3V3: C2.1, C3.1, C5.1, C8.1, C9.1, C10.1, C11.1, R1.1, R2.1, R5.1, R6.1, R7.1, R8.1, R9.1, R10.1, R14.1, R15.1, R20.1, R25.1, SW2.1 (A), TP4.1, U1.3 (3V3), U2.12 (VDD), U3.5 (ADDR), U3.12 (VDD), U7.10 (VCC), U8.5 (VOUT), U9.1 (VCCA), U9.5 (DIR), U10.1 (VCCA)
+5V: C4.1, C13.1, C14.1, TP5.1, U4.2 (VOUT), U4.7 (VOUT), U5.1 (IN), U6.1 (IN), U8.1 (VIN), U8.3 (EN)
BOOT: R2.2, SW1.1, U1.4 (IO0)
CC1_A: J1.A5 (CC1), U2.1 (CC1)
CC1_B: J2.A5 (CC1), U3.1 (CC1)
CC2_A: J1.B5 (CC2), U2.2 (CC2)
CC2_B: J2.B5 (CC2), U3.2 (CC2)
DN_A: J1.A7 (D-), J1.B7 (D-), U7.2 (1D-), U11.3 (I/O2), U11.4 (I/O2)
DN_B: J2.A7 (D-), J2.B7 (D-), U7.4 (2D-), U12.3 (I/O2), U12.4 (I/O2)
DP_A: J1.A6 (D+), J1.B6 (D+), U7.1 (1D+), U11.1 (I/O1), U11.6 (I/O1)
DP_B: J2.A6 (D+), J2.B6 (D+), U7.3 (2D+), U12.1 (I/O1), U12.6 (I/O1)
EN: C1.1, R1.2, TP6.1, U1.45 (EN)
FAULT_A: R14.2, U1.9 (IO5), U5.4 (~FAULT)
FAULT_B: R15.2, U1.35 (IO39), U6.4 (~FAULT)
GND: C1.2, C2.2, C3.2, C4.2, C5.2, C6.2, C7.2, C8.2, C9.2, C10.2, C11.2, C12.2, C13.2, C14.2, C15.2, C16.2, C17.2, C18.2, C19.2, D1.1 (K), J1.A1 (GND), J1.A12 (GND), J1.B1 (GND), J1.B12 (GND), J1.SH (SHIELD), J2.A1 (GND), J2.A12 (GND), J2.B1 (GND), J2.B12 (GND), J2.SH (SHIELD), J3.4, R12.2, R13.2, R16.2, R17.2, R23.2, SW1.2, SW2.4 (TAB), TP3.1, U1.1 (GND), U1.2 (GND), U1.42 (GND), U1.43 (GND), U1.46 (GND), U1.47 (GND), U1.48 (GND), U1.49 (GND), U1.50 (GND), U1.51 (GND), U1.52 (GND), U1.53 (GND), U1.54 (GND), U1.55 (GND), U1.56 (GND), U1.57 (GND), U1.58 (GND), U1.59 (GND), U1.60 (GND), U1.61 (GND), U1.62 (GND), U1.63 (GND), U1.64 (GND), U1.65 (GND), U2.5 (ADDR), U2.10 (GND), U2.11 (~EN), U3.10 (GND), U3.11 (~EN), U4.1 (GND), U4.4 (~ON), U4.5 (GND), U5.2 (GND), U6.2 (GND), U7.5 (GND), U7.6 (~OE), U8.2 (GND), U9.2 (GND), U10.2 (GND), U10.5 (DIR), U11.2 (GND), U12.2 (GND)
I2C_SCL: R6.2, U1.13 (IO9), U2.8 (SCL/OUT2), U3.8 (SCL/OUT2)
I2C_SDA: R5.2, U1.12 (IO8), U2.7 (SDA/OUT1), U3.7 (SDA/OUT1)
ID_A: R8.2, U1.8 (IO4), U2.9 (ID)
ID_B: R9.2, U1.34 (IO38), U3.9 (ID)
ILIM_A: R16.1, U5.5 (ILIM)
ILIM_B: R17.1, U6.5 (ILIM)
J3_RX: J3.2, R19.1
J3_TX: J3.3, R18.2
LED: R24.1, U1.6 (IO2)
LED_A: D1.2 (A), R24.2
MUX_SEL: R11.2, U1.25 (IO21), U7.9 (S)
PWR_ST: R10.2, R11.1, U1.11 (IO7), U4.8 (ST)
RXD0: TP2.1, U1.40 (RXD0)
TGT_RX: R19.2, R21.2, U10.4 (B)
TGT_TX: R18.1, U9.4 (B)
TUSB_INT: R7.2, U1.14 (IO10), U2.6 (~INT/OUT3), U3.6 (~INT/OUT3)
TXD0: TP1.1, U1.39 (TXD0)
UART_RX: R20.2, U1.29 (IO34), U10.3 (A)
UART_TX: R25.2, U1.28 (IO33), U9.3 (A)
USB_DN: U1.23 (USB_D-), U7.7 (D-)
USB_DP: U1.24 (USB_D+), U7.8 (D+)
VBUS_A: C6.1, C15.1, C16.1, J1.A4 (VBUS), J1.A9 (VBUS), J1.B4 (VBUS), J1.B9 (VBUS), R3.1, U4.6 (VIN2), U5.6 (OUT), U11.5 (VBUS)
VBUS_B: C7.1, C17.1, C18.1, J2.A4 (VBUS), J2.A9 (VBUS), J2.B4 (VBUS), J2.B9 (VBUS), R4.1, U4.3 (VIN1), U6.6 (OUT), U12.5 (VBUS)
VBUS_EN_A: R12.1, U1.10 (IO6), U5.3 (EN)
VBUS_EN_B: R13.1, U1.36 (IO40), U6.3 (EN)
VDET_A: R3.2, U2.4 (VBUS_DET)
VDET_B: R4.2, U3.4 (VBUS_DET)
VREF: C12.1, R21.1, R22.1, SW2.2 (COM), U9.6 (VCCB), U10.6 (VCCB)
VREF_EXT: J3.1, SW2.3 (B)
VREF_SENSE: C19.1, R22.2, R23.1, U1.5 (IO1)

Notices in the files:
README.md:
License:
MIT.
The Tailscale and WireGuard protocol code was written from the protocol descriptions and the Tailscale (BSD-3-Clause) and wireguard-go (MIT) sources.
The USB-serial baud-rate encodings were written from FTDI's application note AN232B-05, Silicon Labs' AN571, Espressif's esp-usb VCP drivers (Apache-2.0) and FreeBSD's `uftdi` and `uchcom` drivers (BSD-2-Clause).
